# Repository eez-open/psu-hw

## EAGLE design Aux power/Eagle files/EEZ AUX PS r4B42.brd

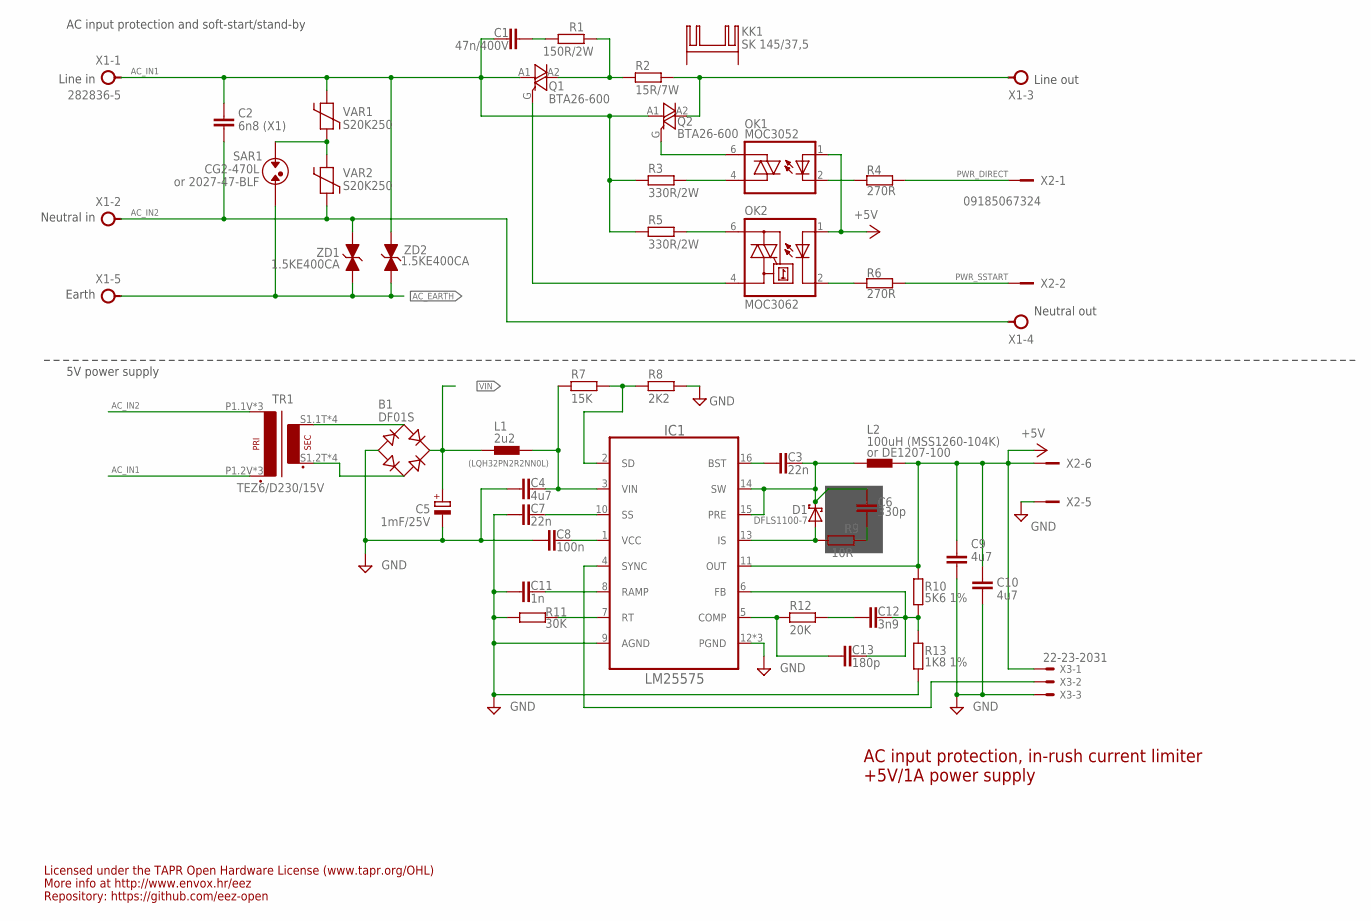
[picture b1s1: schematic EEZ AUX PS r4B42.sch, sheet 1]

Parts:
B1: DF01S; DFS
C1: 47n/400V; C075-052X106
C2: 6n8 (X1); C102-064X133
C3, C7: 22n; C0805
C4, C9, C10: 4u7; C1210
C5: 1mF/25V; ECAP5/10.5
C6: 330p; C0805
C8: 100n; C0805
C11: 1n; C0805
C12: 3n9; C0805
C13: 180p; C0805
D1: DFLS1100-7; SOD123
IC1: LM25575; SOP65P640X110-17N_HOLE
KK1: SK 145/37,5; SK145
L1: 2u2; L1210
L2: 100uH (MSS1260-104K); MSS1278
OK1: MOC3052; DIL6-SMD
OK2: MOC3062; DIL6-SMD; MPN MOC3033S-M
Q1, Q2: BTA26-600; TOP3S-1
R1: 150R/2W; R2512
R2: 15R/7W; R_0913
R3, R5: 330R/2W; R2512
R4, R6: 270R; R0805
R7: 15K; R0805
R8: 2K2; R0805
R9: 10R; R1206
R10: 5K6 1%; R0805
R11: 30K; R0805
R12: 20K; R0805
R13: 1K8 1%; R0805
SAR1: CG2-470L; SAR
TR1: TEZ6/D230/15V; PCB_TRAFO6VA_TEZ+VPP
VAR1, VAR2: S20K250; VARISTOR
X1: 282836-5; TBLOCK5.0_5
X2: 09185067324; IDC-6PIN
X3: 22-23-2031
ZD1, ZD2: 1.5KE400CA; DO201-BIDIR

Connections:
+5V: C9.1, C10.1, IC1.11 (OUT), L2.2, OK1.1 (A), OK2.1 (A), R10.1, X2.6, X3.1; also elsewhere on the board
AC_EARTH: SAR1.P$2, X1.5, ZD1.C (1), ZD2.C (1)
AC_IN1: C1.2, C2.1, Q1.A1, Q2.A1, R3.2, R5.2, TR1.P1.2V (P2), TR1.P2.2V (P2), TR1.P2_TEZ (P2), VAR1.P$2, X1.1, ZD2.A (2)
AC_IN2: C2.2, TR1.P1.1V (P1), TR1.P1_TEZ (P1), TR1.P2.1V (P1), VAR2.P$1, X1.2, X1.4, ZD1.A (2)
DC_PREG1: C4.1, IC1.3 (VIN), L1.2, R7.2
GND: B1.-, C4.2, C5.-, C7.2, C8.1, C9.2, C10.2, C11.1, IC1.9 (AGND), IC1.12 (PGND), IC1.TP (PGND), IC1.TP2 (PGND), R8.1, R11.2, R13.2, X2.5, X3.3; also elsewhere on the board
IS: D1.A, IC1.13 (IS), R9.1
unnamed: C6.2, R9.2
unnamed: OK1.6 (A2), Q2.G
unnamed: OK1.4 (A1), R3.1
unnamed: OK2.4 (A1), Q1.G
unnamed: OK1.2 (C), R4.1
unnamed: OK2.2 (C), R6.1
unnamed: OK2.6 (A2), R5.1
unnamed: Q2.A2, R2.2, X1.3
unnamed: B1.AC1, TR1.S1.1T (S1), TR1.S1.1V (S1), TR1.S2.1T (S1), TR1.S2.1V (S1)
unnamed: IC1.4 (SYNC), X3.2
unnamed: C1.1, R1.1
unnamed: B1.AC2, TR1.S1.2T (S2), TR1.S1.2V (S2), TR1.S2.2T (S2), TR1.S2.2V (S2)
unnamed: Q1.A2, R1.2, R2.1
unnamed: C12.2, R12.2
unnamed: SAR1.P$1, VAR1.P$1, VAR2.P$2
unnamed: C12.1, C13.1, IC1.6 (FB), R10.2, R13.1
unnamed: C3.2, IC1.16 (BST)
unnamed: C13.2, IC1.5 (COMP), R12.1
unnamed: IC1.7 (RT), R11.1
unnamed: C8.2, IC1.1 (VCC)
unnamed: C11.2, IC1.8 (RAMP)
unnamed: C7.1, IC1.10 (SS)
unnamed: IC1.2 (SD), R7.1, R8.2
PWR_DIRECT: R4.2, X2.1
PWR_SSTART: R6.2, X2.2
SW: C3.1, C6.1, D1.C, IC1.14 (SW), IC1.15 (PRE), L2.1
VIN: B1.+, C5.+, L1.1; also elsewhere on the board

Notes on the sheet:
AC input protection, in-rush current limiter
+5V/1A power supply
Line in
Neutral in
Earth
or DE1207-100
Line out
Neutral out
or 2027-47-BLF
(LQH32PN2R2NN0L)
Licensed under the TAPR Open Hardware License (www.tapr.org/OHL)
Repository: https://github.com/eez-open
More info at http://www.envox.hr/eez
5V power supply
AC input protection and soft-start/stand-by

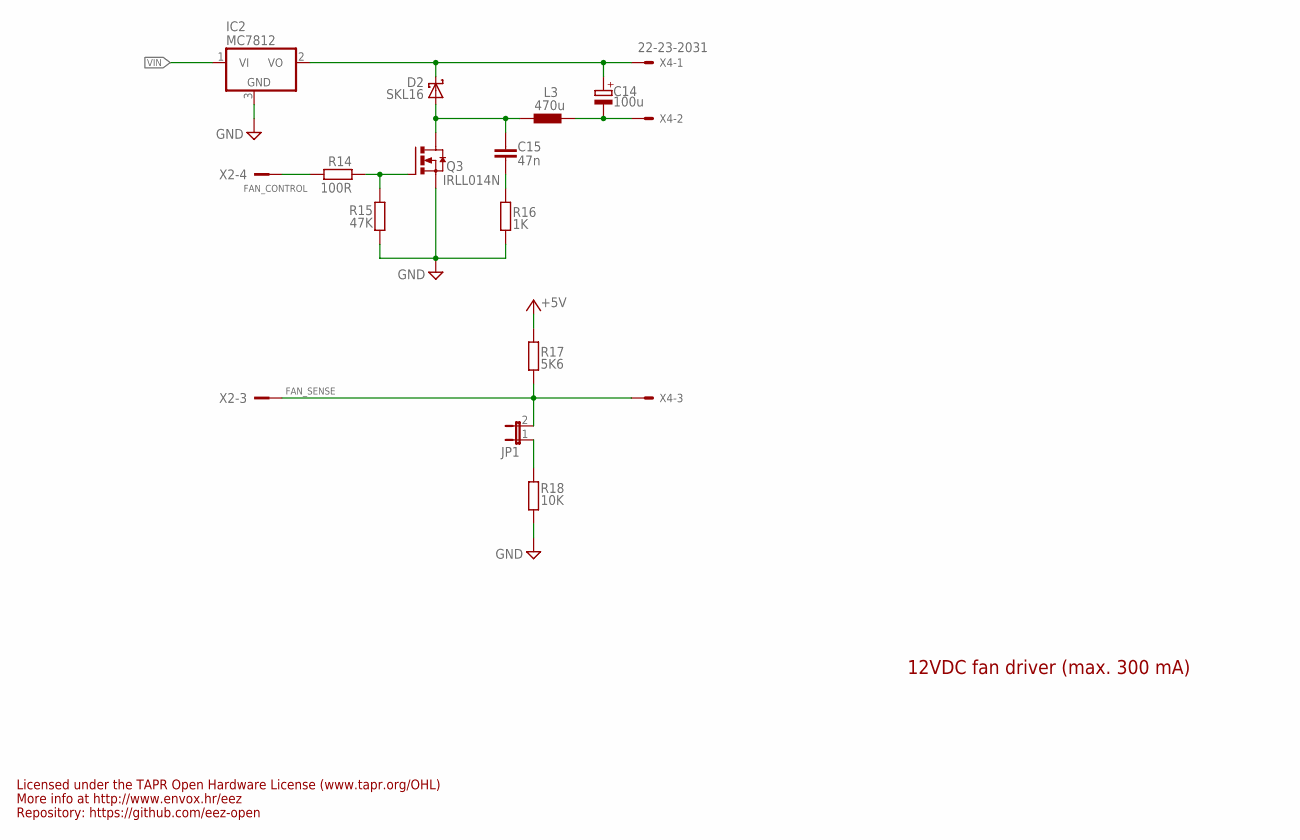
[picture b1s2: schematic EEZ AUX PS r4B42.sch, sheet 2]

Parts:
C14: 100u; CAPAE660X610N
C15: 47n; C0805
D2: SKL16; SOD123
IC2: MC7812; TO252
JP1: JP1E; JP1
L3: 470u; DE0704
Q3: IRLL014N; SOT223
R14: 100R; R0805
R15: 47K; R0805
R16: 1K; R0805
R17: 5K6; R0805
R18: 10K; R0805
X2: 09185067324; IDC-6PIN
X4: 22-23-2031

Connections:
+5V: R17.1; also elsewhere on the board
FAN_CONTROL: R14.2, X2.4
FAN_OUT: C15.2, D2.A, L3.2, Q3.2 (D), Q3.4 (D)
FAN_SENSE: JP1.2, R17.2, X2.3, X4.3
GND: IC2.3 (GND), Q3.3 (S), R15.1, R16.1, R18.2; also elsewhere on the board
unnamed: JP1.1, R18.1
unnamed: C15.1, R16.2
unnamed: Q3.1 (G), R14.1, R15.2
unnamed: C14.1 (+), D2.C, IC2.2 (VO), X4.1
unnamed: C14.2 (-), L3.1, X4.2
VIN: IC2.1 (VI); also elsewhere on the board

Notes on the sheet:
12VDC fan driver (max. 300 mA)
Licensed under the TAPR Open Hardware License (www.tapr.org/OHL)
Repository: https://github.com/eez-open
More info at http://www.envox.hr/eez

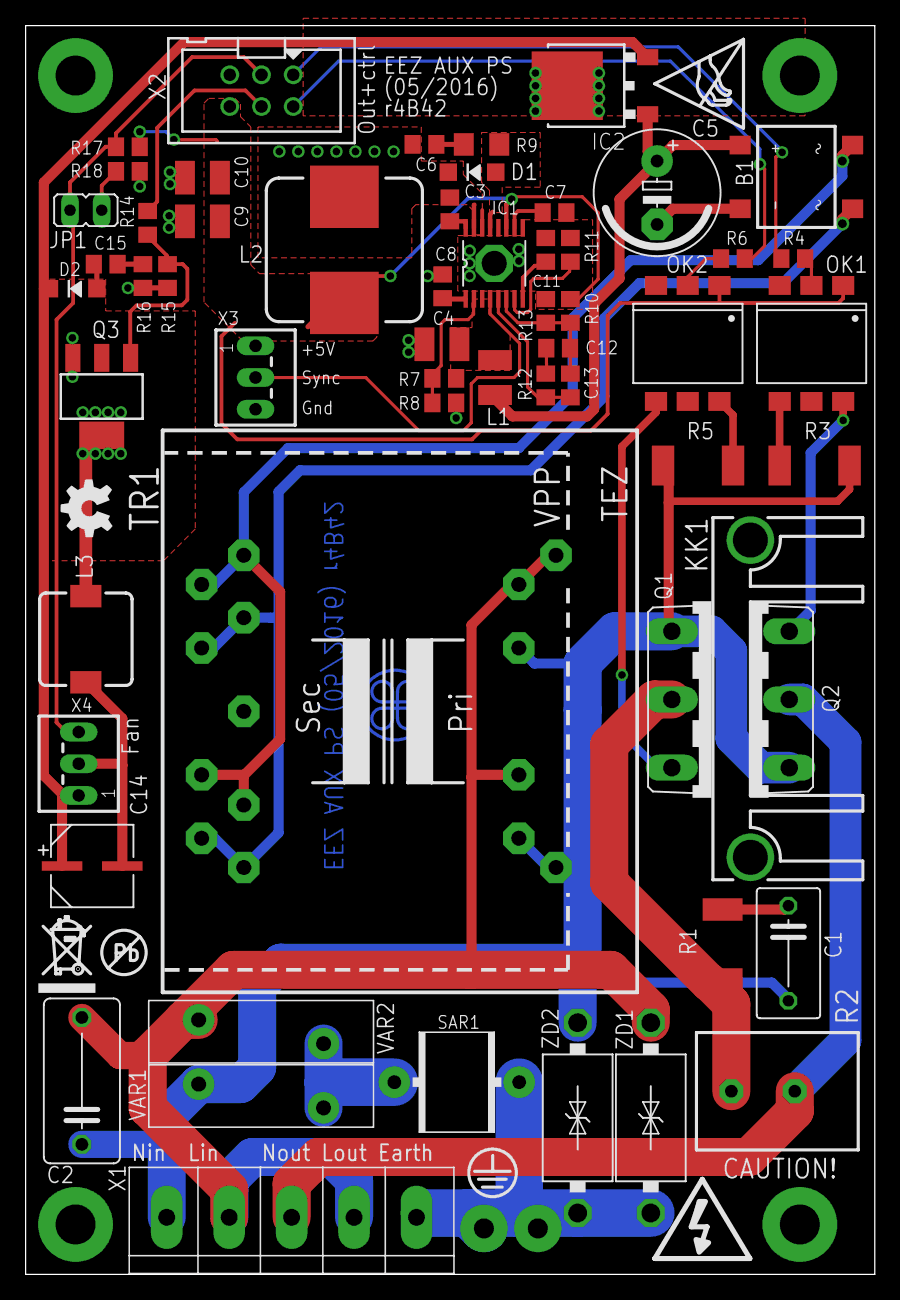
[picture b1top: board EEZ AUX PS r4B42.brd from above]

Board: 3 copper layers, 68.0 x 100.0 mm, 62 parts (0 on the bottom side), 42 nets.

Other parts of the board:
EEZ_SIGNATURE: SIGNATURESMALL; SIGNATURE_5MM
U$2: RECYCLE_BIN1/8
U$3: PB_SMALL
U$4: ESD_SYMBOL
